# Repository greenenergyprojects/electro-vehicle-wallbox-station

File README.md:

# electro-vehicle-wallbox-station
Electro Vehicle Wallbox, Mode 3 / Typ 2 (230V/AC/20A)

## Overview

* Installing Raspberry PI  
  See: [docs/README-install-pi.md](docs/README-install-pi.md)

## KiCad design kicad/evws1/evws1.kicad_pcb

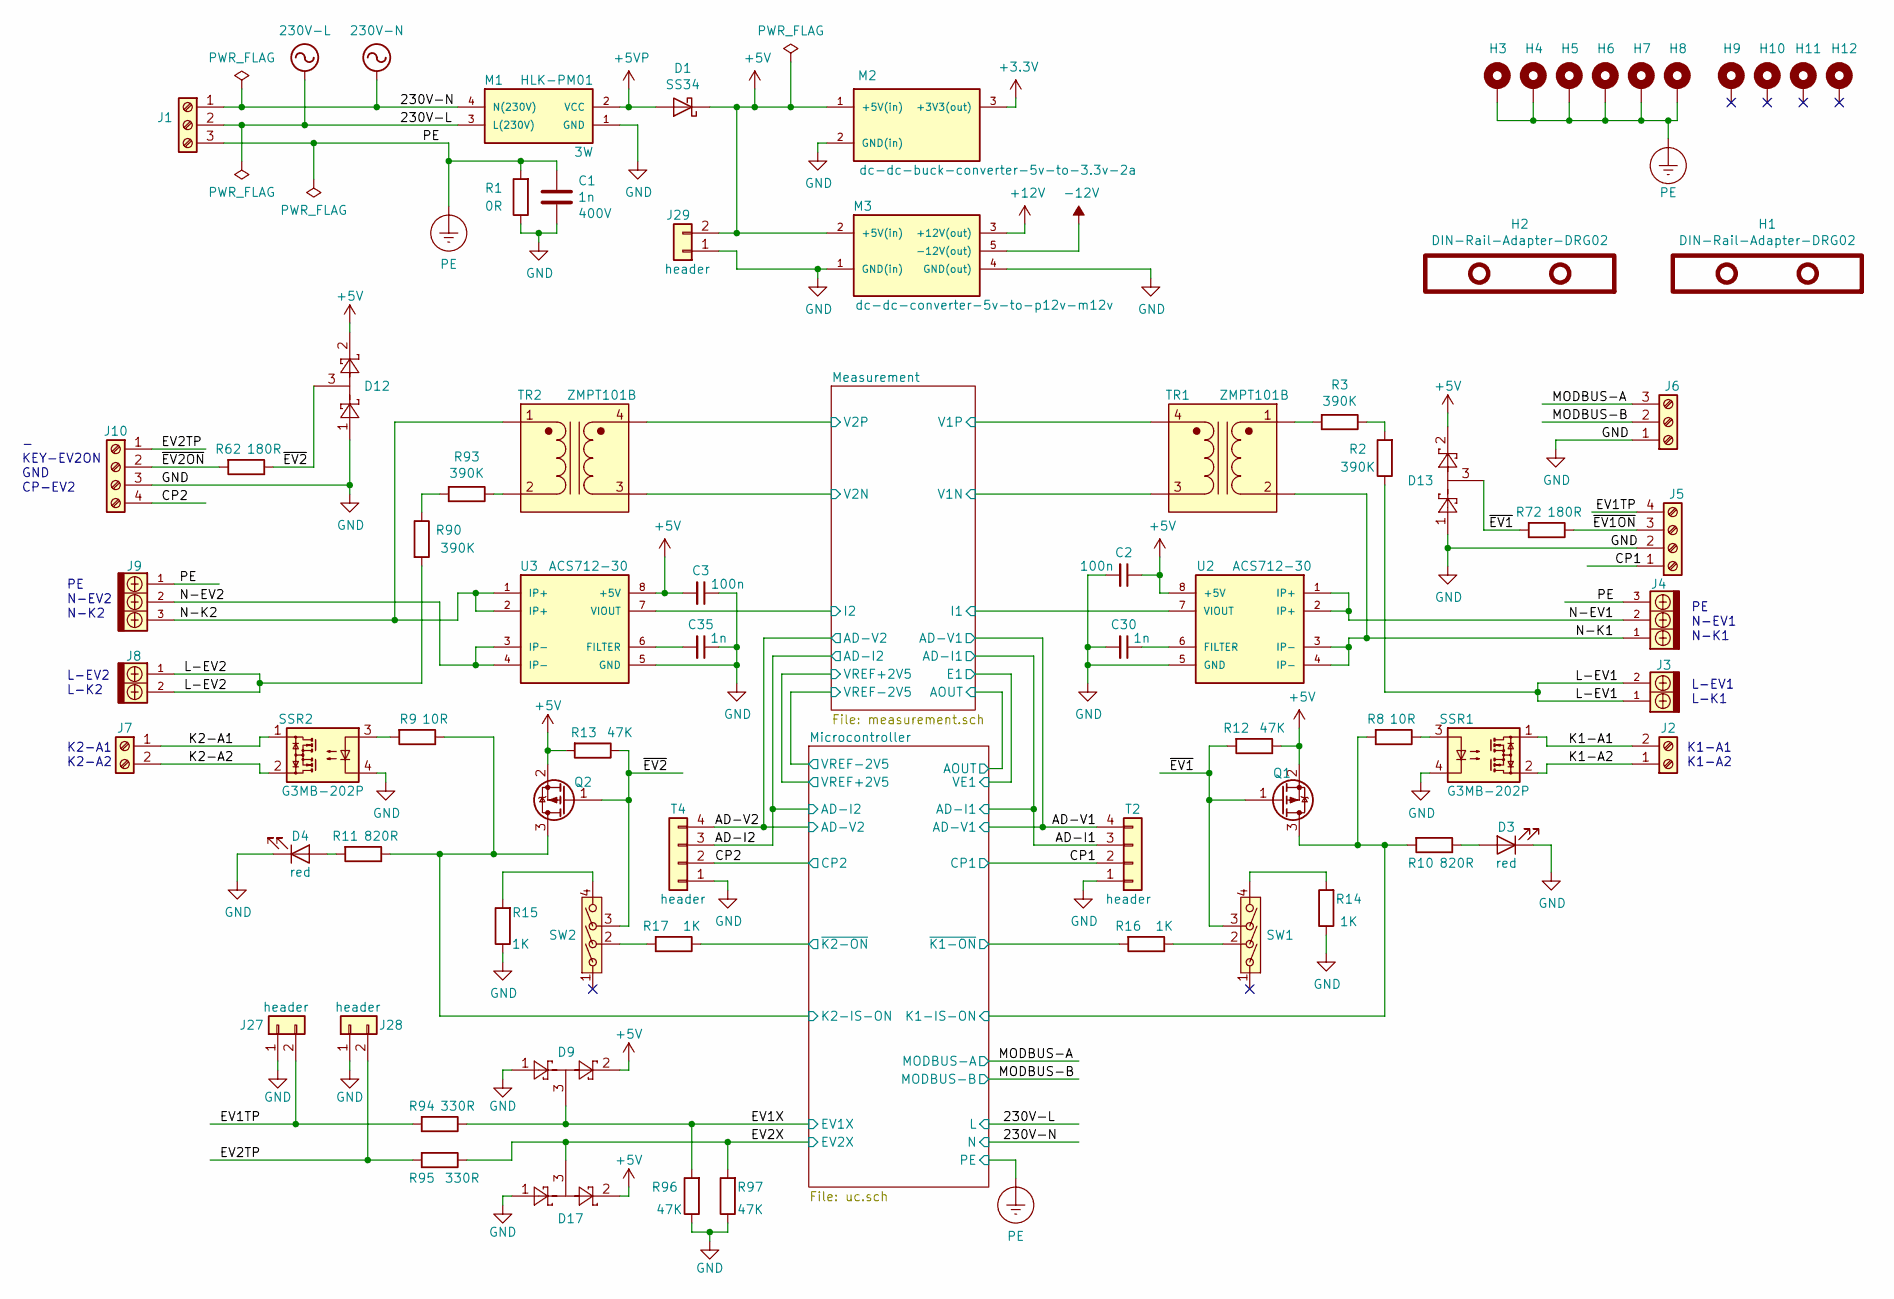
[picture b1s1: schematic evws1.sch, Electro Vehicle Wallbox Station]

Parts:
C1: 1n; c-1206-hand-soldering; Voltage 400V
C2, C3: 100n; c-1206-hand-soldering
C30, C35: 1n; c-1206-hand-soldering
D1: SS34; sma_hand-soldering
D3, D4: LED; LED_0805_HandSoldering
D9, D12, D13, D17: BAT54S; sot-23_hand-soldering
H1, H2: DIN-Rail-Adapter-DRG02; DIN-RAIL-ADAPTER-DRG-02-ebay-254055322883
H3, H4, H5, H6, H7, H8, H9, H10, H11, H12: MountingHole_Pad; MountingHole_2.5mm_Pad_Via
J1, J6: Screw_Terminal_01x03; Terminalblock-5mm-3P
J2, J7: Screw_Terminal_01x02; Terminalblock-5mm-2P
J3, J8: HB9500-2P
J4, J9: HB9500-3P
J5, J10: Screw_Terminal_01x04; Terminalblock-5mm-4P
J27, J28, J29: header; idc-header-1x02-p2.54mm-vertical
M1: HLK-PM01; HLK-PM01-5M05
M2: dc-dc-buck-converter-5v-to-3.3v-2a
M3: dc-dc-converter-5v-to-p12v-m12v
Q1, Q2: AO3401; TSOT-23_HandSoldering
R1: 0R; r-1206-hand-soldering
R2, R3, R90, R93: 390K; r-1206-hand-soldering
R8, R9: 10R; r-1206-hand-soldering
R10, R11: 820R; r-1206-hand-soldering
R12, R13, R96, R97: 47K; r-1206-hand-soldering
R14, R15, R16, R17: 1K; r-1206-hand-soldering
R62, R72: 180R; r-1206-hand-soldering
R94, R95: 330R; r-1206-hand-soldering
SSR1, SSR2: G3MB-202P; SSR_Omron_G3MB-202P
SW1, SW2: SW_SS13F06-G5; Switch-3pos-SS13F06-G5
T2, T4: header; idc-header-1x04-p2.54mm-vertical
TR1, TR2: ZMPT101B; Transformer-zmpt101b_ebay-121438904988
U2, U3: ACS712-30; ACS712

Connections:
230V-L: J1.2, M1.3 (L(230V)); also elsewhere on the board
230V-N: J1.1, M1.4 (N(230V)); also elsewhere on the board
+5V: C2.1, C3.2, D1.1 (K), D9.2, D12.2, D13.2, D17.2, J29.2, M2.1 (+5V(in)), M3.2 (+5V(in)), Q1.2 (S), Q2.2 (S), R12.1, R13.2, U2.8 (+5V), U3.8 (+5V); also elsewhere on the board
+5VP: D1.2 (A), M1.2 (VCC)
+12V: M3.3 (+12V(out)); also elsewhere on the board
-12V: M3.5 (-12V(out)); also elsewhere on the board
/AD-I1: T2.3; also elsewhere on the board
/AD-I2: T4.3; also elsewhere on the board
/AD-V1: T2.4; also elsewhere on the board
/AD-V2: T4.4; also elsewhere on the board
/CP1: J5.1, T2.2; also elsewhere on the board
/CP2: J10.4, T4.2; also elsewhere on the board
/EV1TP: J5.4, J27.2, R94.2
/EV1X: D9.3, R94.1, R96.2; also elsewhere on the board
/EV2TP: J10.1, J28.2, R95.2
/EV2X: D17.3, R95.1, R97.2; also elsewhere on the board
/K1-A1: J2.2, SSR1.1 (AC)
/K1-A2: J2.1, SSR1.2 (AC)
/K2-A1: J7.1, SSR2.1 (AC)
/K2-A2: J7.2, SSR2.2 (AC)
/L-EV1: J3.1, J3.2, R2.1
/L-EV2: J8.1, J8.2, R90.2
/MODBUS-A: J6.3; also elsewhere on the board
/MODBUS-B: J6.2; also elsewhere on the board
/Measurement/I1: U2.7 (VIOUT); also elsewhere on the board
/Measurement/I2: U3.7 (VIOUT); also elsewhere on the board
/Measurement/V1P: TR1.4 (SB); also elsewhere on the board
/Measurement/V2P: TR2.4 (SB); also elsewhere on the board
/Microcontroller/K1-IS-ON: Q1.3 (D), R8.2, R10.2; also elsewhere on the board
/Microcontroller/K2-IS-ON: Q2.3 (D), R9.1, R11.1; also elsewhere on the board
/Microcontroller/~K1-ON: R16.2; also elsewhere on the board
/Microcontroller/~K2-ON: R17.1; also elsewhere on the board
/N-EV1: J4.2, U2.1 (IP+), U2.2 (IP+)
/N-EV2: J9.2, U3.3 (IP-), U3.4 (IP-)
/N-K1: J4.1, TR1.2 (AB), U2.3 (IP-), U2.4 (IP-)
/N-K2: J9.3, TR2.1 (AA), U3.1 (IP+), U3.2 (IP+)
/~EV1: D13.3, Q1.1 (G), R12.2, R72.2, SW1.3
/~EV1ON: J5.3, R72.1
/~EV2: D12.3, Q2.1 (G), R13.1, R62.1, SW2.3
/~EV2ON: J10.2, R62.2
GND: C1.2, C2.2, C3.1, C30.2, C35.1, D3.1 (K), D4.1 (K), D9.1, D12.1, D13.1, D17.1, J5.2, J6.1, J10.3, J27.1, J28.1, J29.1, M1.1 (GND), M2.2 (GND(in)), M3.1 (GND(in)), M3.4 (GND(out)), R1.1, R14.1, R15.1, R96.1, R97.1, SSR1.4 (-), SSR2.4 (-), T2.1, T4.1, TR1.3 (SA), TR2.3 (SA), U2.5 (GND), U3.5 (GND); also elsewhere on the board
unnamed: C30.1, U2.6 (FILTER)
unnamed: C35.2, U3.6 (FILTER)
unnamed: D3.2 (A), R10.1
unnamed: D4.2 (A), R11.2
unnamed: R2.2, R3.1
unnamed: R3.2, TR1.1 (AA)
unnamed: R8.1, SSR1.3 (+)
unnamed: R9.2, SSR2.3 (+)
unnamed: R14.2, SW1.4
unnamed: R15.2, SW2.4
unnamed: R16.1, SW1.2
unnamed: R17.2, SW2.2
unnamed: R90.1, R93.2
unnamed: R93.1, TR2.2 (AB)
PE: C1.1, H3.1, H4.1, H5.1, H6.1, H7.1, H8.1, J1.3, J4.3, J9.1, R1.2; also elsewhere on the board

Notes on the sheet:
L-EV2 L-K2
PE N-EV2 N-K2
K2-A1 K2-A2
- KEY-EV2ON GND CP-EV2
L-EV1 L-K1
PE N-EV1 N-K1
K1-A1 K1-A2

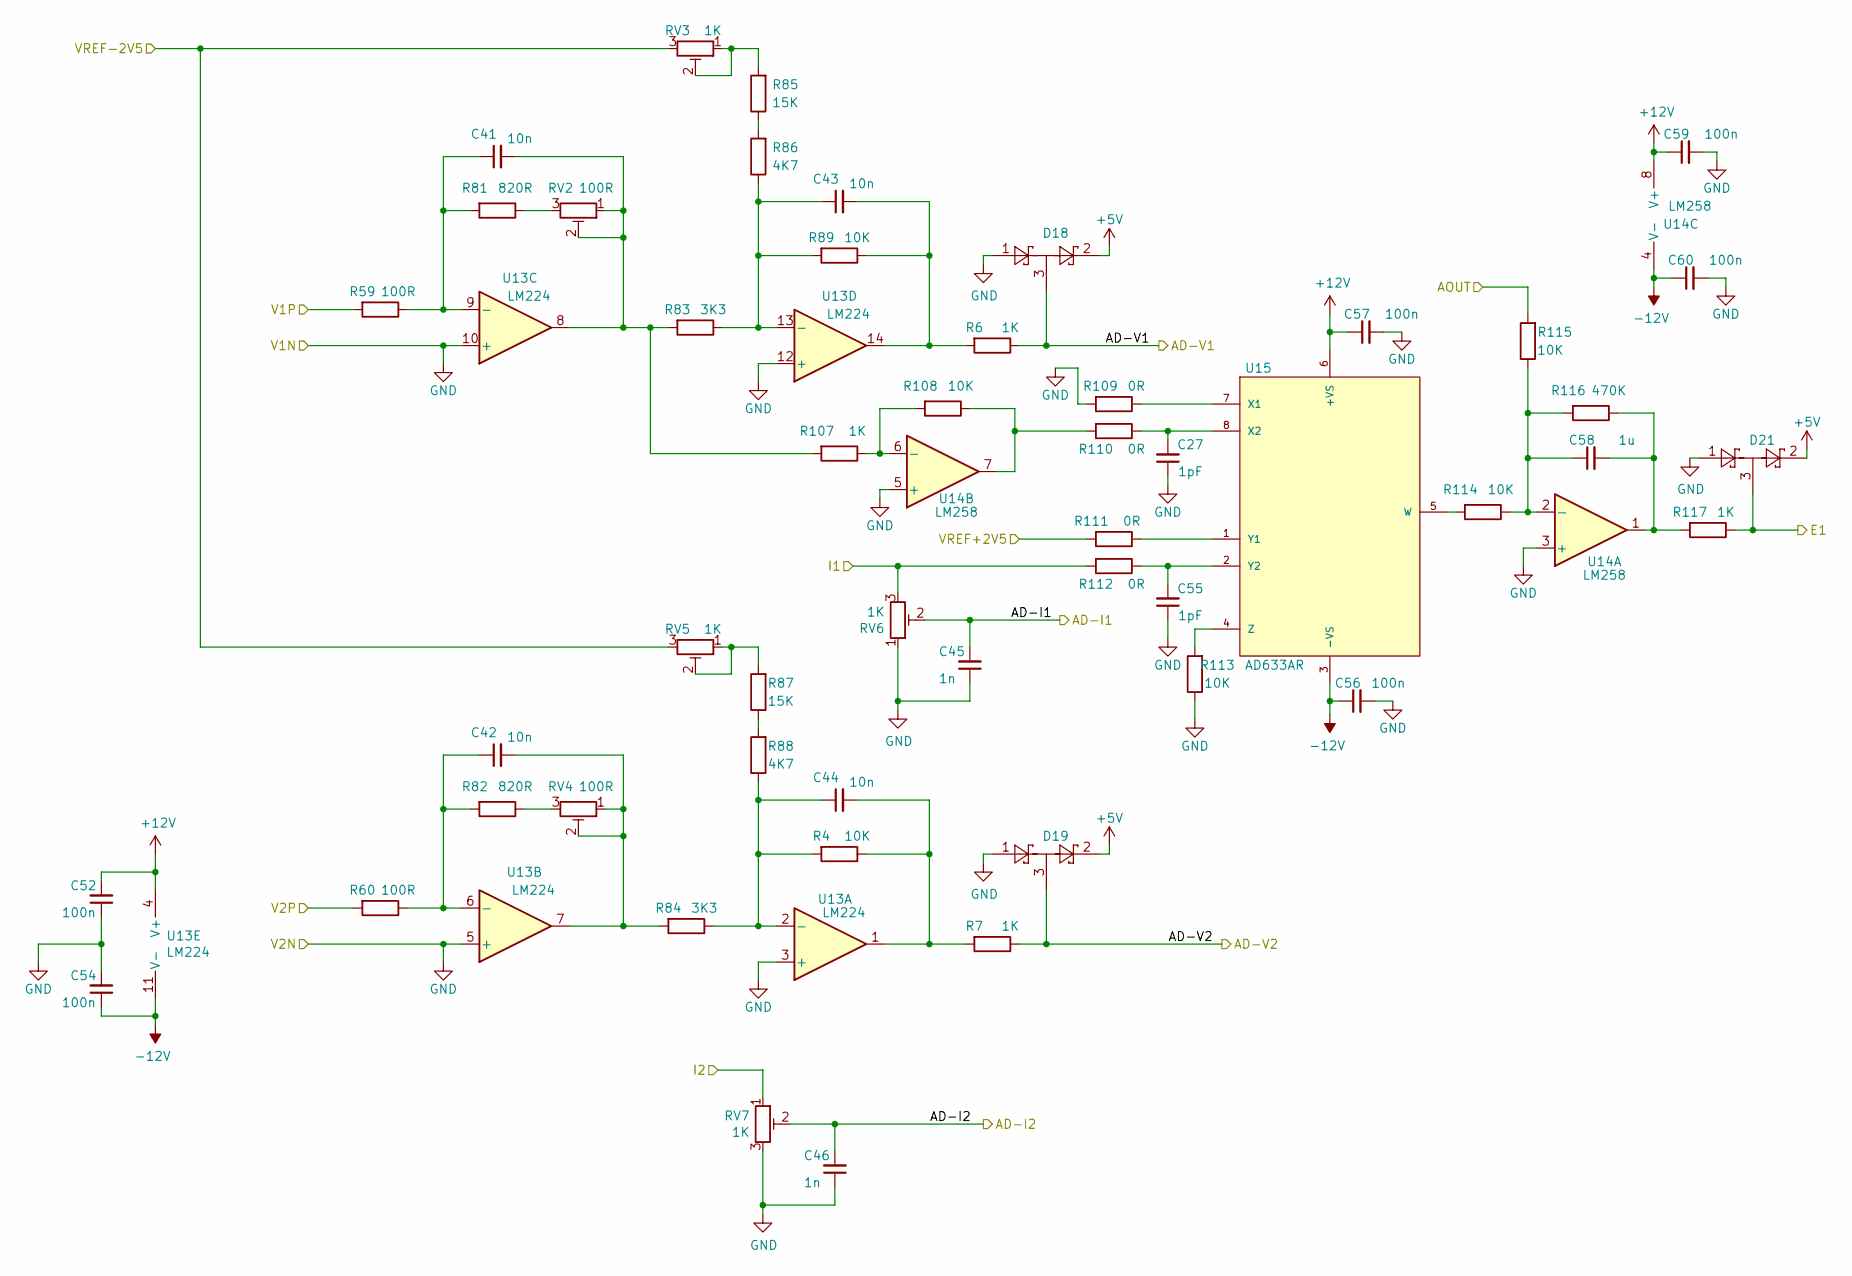
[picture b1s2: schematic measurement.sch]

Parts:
C27, C55: 1pF; c-1206-hand-soldering
C41, C42, C43, C44: 10n; c-1206-hand-soldering
C45, C46: 1n; c-1206-hand-soldering
C52, C54, C56, C57, C59, C60: 100n; c-1206-hand-soldering
C58: 1u; c-1206-hand-soldering
D18, D19, D21: BAT54S; sot-23_hand-soldering
R4, R89, R108, R113, R114, R115: 10K; r-1206-hand-soldering
R6, R7, R107, R117: 1K; r-1206-hand-soldering
R59, R60: 100R; r-1206-hand-soldering
R81, R82: 820R; r-1206-hand-soldering
R83, R84: 3K3; r-1206-hand-soldering
R85, R87: 15K; r-1206-hand-soldering
R86, R88: 4K7; r-1206-hand-soldering
R109, R110, R111, R112: 0R; r-1206-hand-soldering
R116: 470K; r-1206-hand-soldering
RV2, RV4: 100R; trimmer-tht-3296
RV3, RV5, RV6, RV7: 1K; trimmer-tht-3296
U13: LM224; soic-14_hand-soldering
U14: LM258; soic-8_hand-soldering
U15: AD633AR; soic-8_hand-soldering

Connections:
+5V: D18.2, D19.2, D21.2; also elsewhere on the board
+12V: C52.2, C57.1, C59.1, U13.4 (V+), U14.8 (V+), U15.6 (+VS); also elsewhere on the board
-12V: C54.1, C56.1, C60.1, U13.11 (V-), U14.4 (V-), U15.3 (-VS); also elsewhere on the board
/AD-I1: C45.2, RV6.2; also elsewhere on the board
/AD-I2: C46.2, RV7.2; also elsewhere on the board
/AD-V1: D18.3, R6.1; also elsewhere on the board
/AD-V2: D19.3, R7.1; also elsewhere on the board
/Measurement/AOUT: R115.2; also elsewhere on the board
/Measurement/E1: D21.3, R117.1; also elsewhere on the board
/Measurement/I1: R112.2, RV6.3; also elsewhere on the board
/Measurement/I2: RV7.1; also elsewhere on the board
/Measurement/V1P: R59.2; also elsewhere on the board
/Measurement/V2P: R60.2; also elsewhere on the board
/Measurement/VREF+2V5: R111.2; also elsewhere on the board
/Measurement/VREF-2V5: RV3.3, RV5.3; also elsewhere on the board
GND: C27.1, C45.1, C46.1, C52.1, C54.2, C55.1, C56.2, C57.2, C59.2, C60.2, D18.1, D19.1, D21.1, R109.2, R113.1, RV6.1, RV7.3, U13.3 (+), U13.5 (+), U13.10 (+), U13.12 (+), U14.3 (+), U14.5 (+); also elsewhere on the board
unnamed: C27.2, R110.1, U15.8 (X2)
unnamed: C41.1, R59.1, R81.2, U13.9 (-)
unnamed: C41.2, R83.2, R107.2, RV2.1, RV2.2, U13.8
unnamed: C42.1, R60.1, R82.2, U13.6 (-)
unnamed: C42.2, R84.2, RV4.1, RV4.2, U13.7
unnamed: C43.1, R83.1, R86.1, R89.2, U13.13 (-)
unnamed: C43.2, R6.2, R89.1, U13.14
unnamed: C44.1, R4.2, R84.1, R88.1, U13.2 (-)
unnamed: C44.2, R4.1, R7.2, U13.1
unnamed: C55.2, R112.1, U15.2 (Y2)
unnamed: C58.1, R114.1, R115.1, R116.2, U14.2 (-)
unnamed: C58.2, R116.1, R117.2, U14.1
unnamed: R81.1, RV2.3
unnamed: R82.1, RV4.3
unnamed: R85.1, R86.2
unnamed: R85.2, RV3.1, RV3.2
unnamed: R87.1, R88.2
unnamed: R87.2, RV5.1, RV5.2
unnamed: R107.1, R108.2, U14.6 (-)
unnamed: R108.1, R110.2, U14.7
unnamed: R109.1, U15.7 (X1)
unnamed: R111.1, U15.1 (Y1)
unnamed: R113.2, U15.4 (Z)
unnamed: R114.2, U15.5 (W)

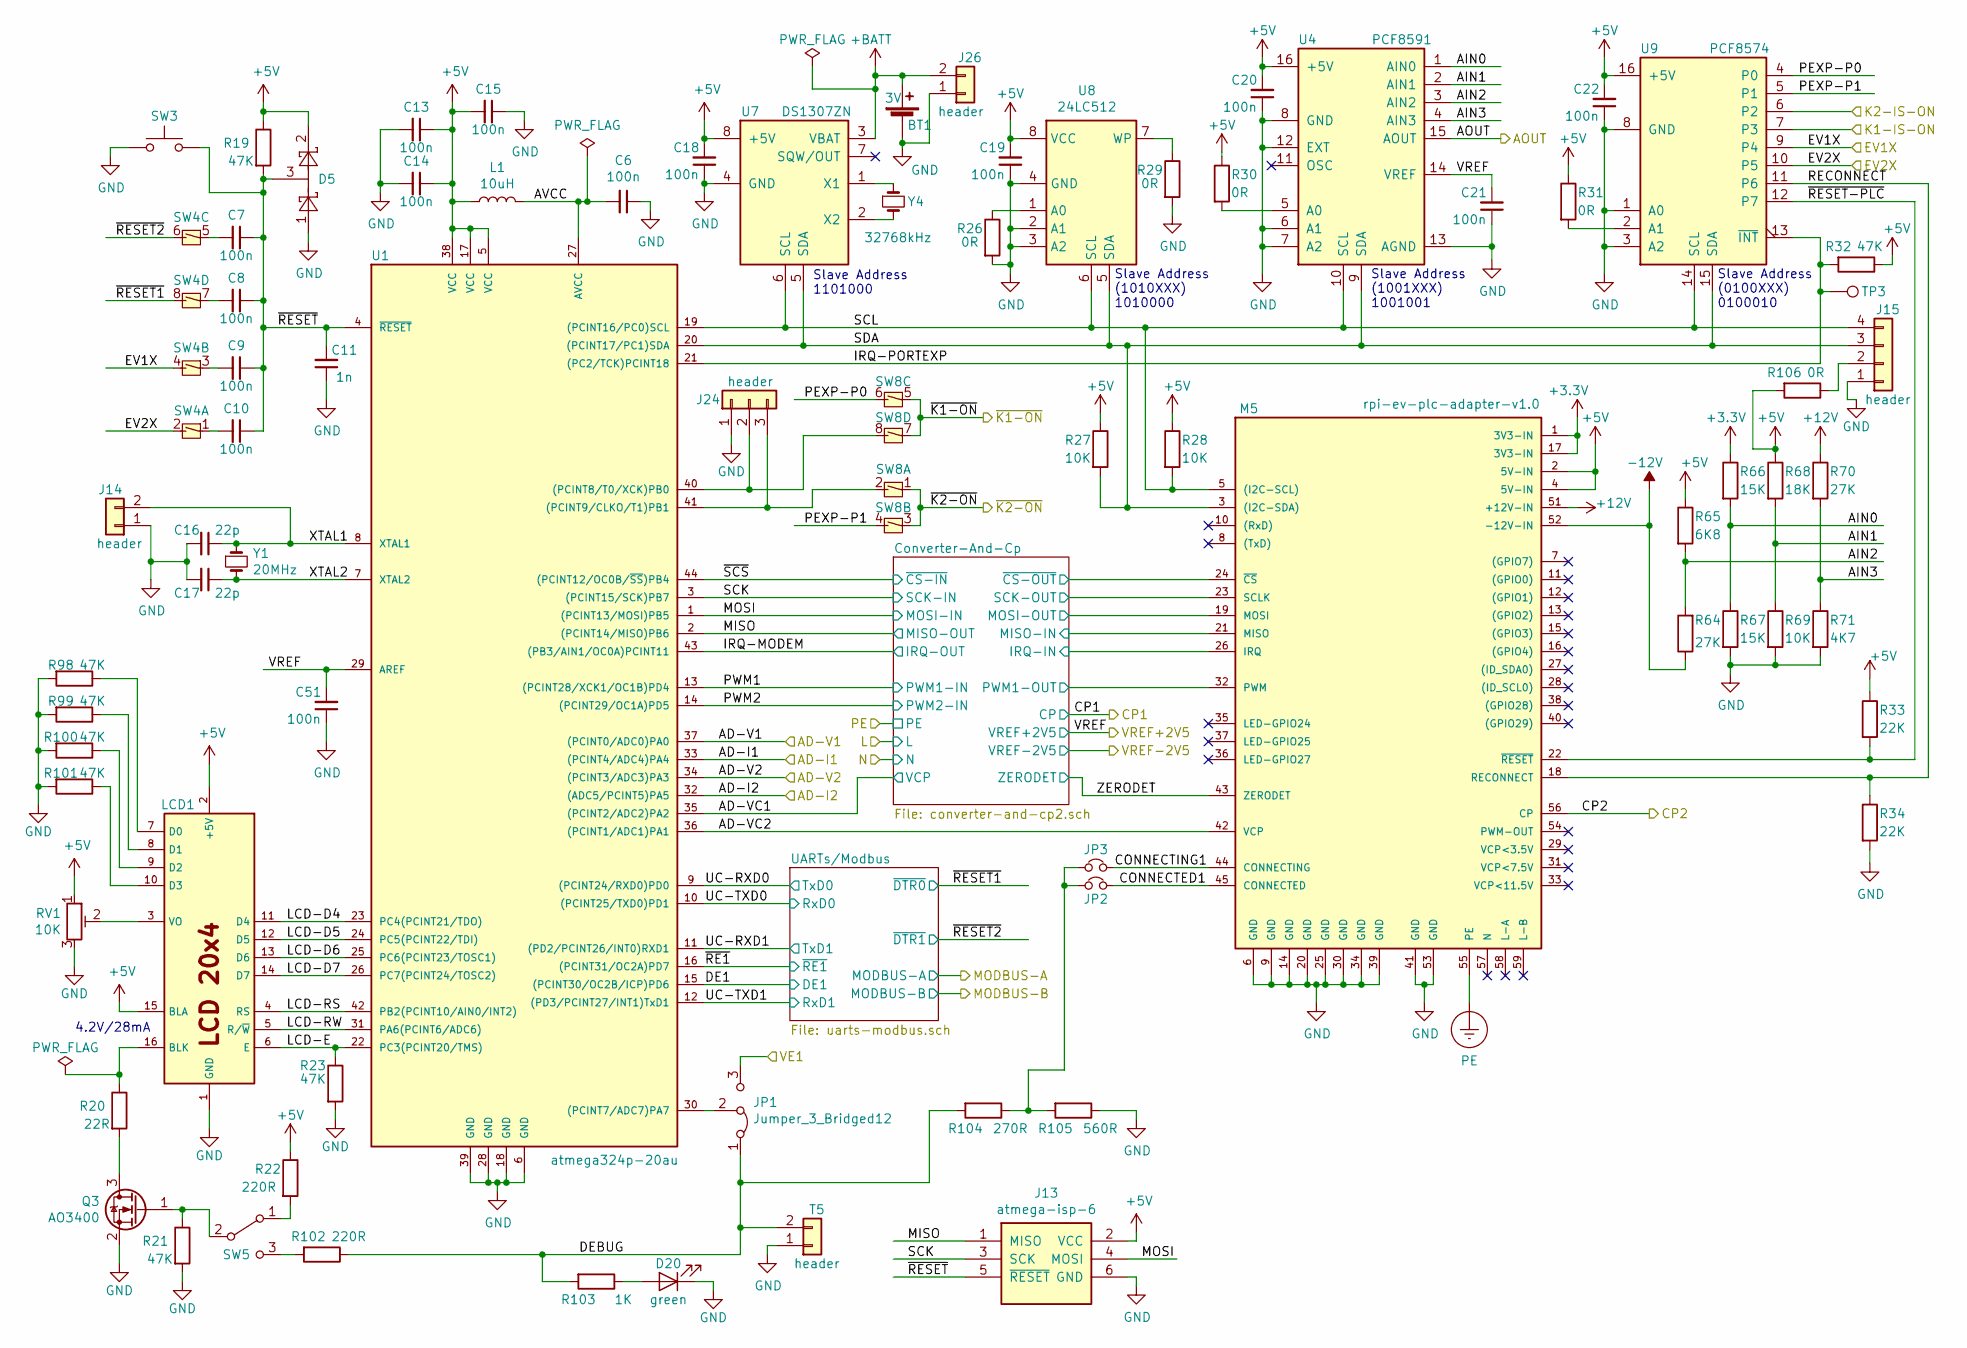
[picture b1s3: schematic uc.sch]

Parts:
BT1: 3V; knob-battery-holder-vertical-tht
C6, C7, C8, C9, C10, C13, C14, C15, C18, C19, C20, C21, C22, C51: 100n; c-1206-hand-soldering
C11: 1n; c-1206-hand-soldering
C16, C17: 22p; c-1206-hand-soldering
D5: BAT54S; sot-23_hand-soldering
D20: LED; LED_0805_HandSoldering
J13: atmega-isp-6; AVR-ISP-6
J14, J26: header; idc-header-1x02-p2.54mm-vertical
J15: header; idc-header-1x04-p2.54mm-vertical
J24: header; idc-header-1x03-p2.54mm-vertical
JP1: Jumper_3_Bridged12; idc-header-1x03-p2.54mm-vertical
JP2, JP3: header; idc-header-1x02-p2.54mm-vertical
L1: 10uH; L_1206_HandSoldering
LCD1: lcd-4x20-5v-backlight-4bit
M5: rpi-ev-plc-adapter-v1.0
Q3: AO3400; sot-23_hand-soldering
R19, R21, R23, R32, R98, R99, R100, R101: 47K; r-1206-hand-soldering
R20: 22R; r-1206-hand-soldering
R22, R102: 220R; r-1206-hand-soldering
R26, R29, R30, R31, R106: 0R; r-1206-hand-soldering
R27, R28, R69: 10K; r-1206-hand-soldering
R33, R34: 22K; r-1206-hand-soldering
R64, R70: 27K; r-1206-hand-soldering
R65: 6K8; r-1206-hand-soldering
R66, R67: 15K; r-1206-hand-soldering
R68: 18K; r-1206-hand-soldering
R71: 4K7; r-1206-hand-soldering
R103: 1K; r-1206-hand-soldering
R104: 270R; r-1206-hand-soldering
R105: 560R; r-1206-hand-soldering
RV1: 10K; trimmer-tht-3296
SW3: SW_Push; push-button-smd-4.5x4.5mm-black
SW4, SW8: dip-switch-4x2pos-smd-1.27mm
SW5: SS-12D00G3; switch_ss-12d00g3
T5: header; idc-header-1x02-p2.54mm-vertical
TP3: TestPoint; Measurement_Point_Round-TH_Small
U1: atmega324p-20au; TQFP-44_10x10mm_Pitch0.8mm
U4: PCF8591; soic-16w_hand-soldering
U7: DS1307ZN; soic-8_hand-soldering
U8: 24LC512; soic-8_hand-soldering
U9: PCF8574; soic-16w_hand-soldering
Y1: 20MHz; hc49s-smd
Y4: 32768kHz; crystal-32.768khz-2x6mm-tht-vertical

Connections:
+5V: C13.1, C14.1, C15.2, C18.2, C19.2, C20.2, C22.2, D5.2, J13.2 (VCC), L1.1, LCD1.2 (+5V), LCD1.15 (BLA), M5.2 (5V-IN), M5.4 (5V-IN), R19.1, R22.1, R27.1, R28.1, R30.1, R31.1, R32.1, R33.1, R65.1, R68.1, R106.2, RV1.1, U1.5 (VCC), U1.17 (VCC), U1.38 (VCC), U4.16 (+5V), U7.8 (+5V), U8.8 (VCC), U9.16 (+5V); also elsewhere on the board
+12V: M5.51 (+12V-IN), R70.1; also elsewhere on the board
+BATT: BT1.1 (+), J26.2, U7.3 (VBAT)
-12V: M5.52 (-12V-IN), R64.1; also elsewhere on the board
/AD-I1: U1.33 ((PCINT4/ADC4)PA4); also elsewhere on the board
/AD-I2: U1.32 ((ADC5/PCINT5)PA5); also elsewhere on the board
/AD-V1: U1.37 ((PCINT0/ADC0)PA0); also elsewhere on the board
/AD-V2: U1.34 ((PCINT3/ADC3)PA3); also elsewhere on the board
/CP2: M5.56 (CP); also elsewhere on the board
/EV1X: SW4.4, U9.9 (P4); also elsewhere on the board
/EV2X: SW4.2, U9.10 (P5); also elsewhere on the board
/Measurement/AOUT: U4.15 (AOUT); also elsewhere on the board
/Measurement/E1: JP1.3 (B); also elsewhere on the board
/Measurement/VREF+2V5: C21.2, C51.2, U1.29 (AREF), U4.14 (VREF); also elsewhere on the board
/Microcontroller/AD-VC1: U1.35 ((PCINT2/ADC2)PA2); also elsewhere on the board
/Microcontroller/AD-VC2: M5.42 (VCP), U1.36 ((PCINT1/ADC1)PA1)
/Microcontroller/AIN0: R66.2, R67.1, U4.1 (AIN0)
/Microcontroller/AIN1: R68.2, R69.1, U4.2 (AIN1)
/Microcontroller/AIN2: R64.2, R65.2, U4.3 (AIN2)
/Microcontroller/AIN3: R70.2, R71.1, U4.4 (AIN3)
/Microcontroller/AVCC: C6.2, L1.2, U1.27 (AVCC)
/Microcontroller/CONNECTED1: JP2.2, M5.45 (CONNECTED)
/Microcontroller/CONNECTING1: JP3.2, M5.44 (CONNECTING)
/Microcontroller/Converter-And-Cp/IRQ-IN: M5.26 (IRQ); also elsewhere on the board
/Microcontroller/Converter-And-Cp/MISO-IN: M5.21 (MISO); also elsewhere on the board
/Microcontroller/Converter-And-Cp/MOSI-OUT: M5.19 (MOSI); also elsewhere on the board
/Microcontroller/Converter-And-Cp/PWM1-OUT: M5.32 (PWM); also elsewhere on the board
/Microcontroller/Converter-And-Cp/SCK-OUT: M5.23 (SCLK); also elsewhere on the board
/Microcontroller/Converter-And-Cp/~CS-OUT: M5.24 (~CS); also elsewhere on the board
/Microcontroller/DE1: U1.15 ((PCINT30/OC2B/ICP)PD6); also elsewhere on the board
/Microcontroller/DEBUG: JP1.1 (A), R102.1, R103.2, R104.2, T5.2
/Microcontroller/IRQ-MODEM: U1.43 ((PB3/AIN1/OC0A)PCINT11); also elsewhere on the board
/Microcontroller/IRQ-PORTEXP: R32.2, TP3.1, U1.21 ((PC2/TCK)PCINT18), U9.13 (~INT~)
/Microcontroller/K1-IS-ON: U9.7 (P3); also elsewhere on the board
/Microcontroller/K2-IS-ON: U9.6 (P2); also elsewhere on the board
/Microcontroller/LCD-D4: LCD1.11 (D4), U1.23 (PC4(PCINT21/TDO))
/Microcontroller/LCD-D5: LCD1.12 (D5), U1.24 (PC5(PCINT22/TDI))
/Microcontroller/LCD-D6: LCD1.13 (D6), U1.25 (PC6(PCINT23/TOSC1))
/Microcontroller/LCD-D7: LCD1.14 (D7), U1.26 (PC7(PCINT24/TOSC2))
/Microcontroller/LCD-E: LCD1.6 (E), R23.1, U1.22 (PC3(PCINT20/TMS))
/Microcontroller/LCD-RS: LCD1.4 (RS), U1.42 (PB2(PCINT10/AIN0/INT2))
/Microcontroller/LCD-RW: LCD1.5 (R/~W~), U1.31 (PA6(PCINT6/ADC6))
/Microcontroller/MISO: J13.1 (MISO), U1.2 ((PCINT14/MISO)PB6); also elsewhere on the board
/Microcontroller/MOSI: J13.4 (MOSI), U1.1 ((PCINT13/MOSI)PB5); also elsewhere on the board
/Microcontroller/PEXP-P0: SW8.6 (4), U9.4 (P0)
/Microcontroller/PEXP-P1: SW8.4, U9.5 (P1)
/Microcontroller/PWM1: U1.13 ((PCINT28/XCK1/OC1B)PD4); also elsewhere on the board
/Microcontroller/PWM2: U1.14 ((PCINT29/OC1A)PD5); also elsewhere on the board
/Microcontroller/RECONNECT: M5.18 (RECONNECT), R34.1, U9.11 (P6)
/Microcontroller/SCK: J13.3 (SCK), U1.3 ((PCINT15/SCK)PB7); also elsewhere on the board
/Microcontroller/SCL: J15.4, M5.5 ((I2C-SCL)), R28.2, U1.19 ((PCINT16/PC0)SCL), U4.10 (SCL), U7.6 (SCL), U8.6 (SCL), U9.14 (SCL)
/Microcontroller/SDA: J15.3, M5.3 ((I2C-SDA)), R27.2, U1.20 ((PCINT17/PC1)SDA), U4.9 (SDA), U7.5 (SDA), U8.5 (SDA), U9.15 (SDA)
/Microcontroller/UC-RXD0: U1.9 ((PCINT24/RXD0)PD0); also elsewhere on the board
/Microcontroller/UC-RXD1: U1.11 ((PD2/PCINT26/INT0)RXD1); also elsewhere on the board
/Microcontroller/UC-TXD0: U1.10 ((PCINT25/TXD0)PD1); also elsewhere on the board
/Microcontroller/UC-TXD1: U1.12 ((PD3/PCINT27/INT1)TxD1); also elsewhere on the board
/Microcontroller/XTAL1: C16.1, J14.2, U1.8 (XTAL1), Y1.1
/Microcontroller/XTAL2: C17.1, U1.7 (XTAL2), Y1.2
/Microcontroller/ZERODET: M5.43 (ZERODET); also elsewhere on the board
/Microcontroller/~K1-ON: SW8.5 (3), SW8.7 (3); also elsewhere on the board
/Microcontroller/~K2-ON: SW8.1, SW8.3; also elsewhere on the board
/Microcontroller/~RE1: U1.16 ((PCINT31/OC2A)PD7); also elsewhere on the board
/Microcontroller/~RESET: C7.1, C8.1, C9.1, C10.1, C11.2, D5.3, J13.5 (~RESET~), R19.2, SW3.2, U1.4 (~RESET)
/Microcontroller/~RESET1: SW4.8 (4); also elsewhere on the board
/Microcontroller/~RESET2: SW4.6 (4); also elsewhere on the board
/Microcontroller/~RESET-PLC: M5.22 (~RESET), R33.2, U9.12 (P7)
/Microcontroller/~SCS: U1.44 ((PCINT12/OC0B/~SS~)PB4); also elsewhere on the board
GND: BT1.2 (-), C6.1, C11.1, C13.2, C14.2, C15.1, C16.2, C17.2, C18.1, C19.1, C20.1, C21.1, C22.1, C51.1, D5.1, D20.1 (K), J13.6 (GND), J14.1, J15.1, J24.1, J26.1, LCD1.1 (GND), M5.6 (GND), M5.9 (GND), M5.14 (GND), M5.20 (GND), M5.25 (GND), M5.30 (GND), M5.34 (GND), M5.39 (GND), M5.41 (GND), M5.53 (GND), Q3.2 (S), R21.2, R23.2, R26.2, R29.2, R34.2, R67.2, R69.2, R71.2, R98.2, R99.2, R100.2, R101.2, R105.1, RV1.3, SW3.1, T5.1, U1.6 (GND), U1.18 (GND), U1.28 (GND), U1.39 (GND), U4.6 (A1), U4.7 (A2), U4.8 (GND), U4.12 (EXT), U4.13 (AGND), U7.4 (GND), U8.2 (A1), U8.3 (A2), U8.4 (GND), U9.1 (A0), U9.3 (A2), U9.8 (GND); also elsewhere on the board
unnamed: C7.2, SW4.5 (3)
unnamed: C8.2, SW4.7 (3)
unnamed: C9.2, SW4.3
unnamed: C10.2, SW4.1
unnamed: D20.2 (A), R103.1
unnamed: J15.2, R106.1
unnamed 147: J24.2, SW8.8 (4), U1.40 ((PCINT8/T0/XCK)PB0); also elsewhere on the board
unnamed 148: J24.3, SW8.2, U1.41 ((PCINT9/CLKO/T1)PB1); also elsewhere on the board
unnamed: JP1.2 (C), U1.30 ((PCINT7/ADC7)PA7)
unnamed: JP2.1, JP3.1, R104.1, R105.2
unnamed: LCD1.3 (VO), RV1.2
unnamed: LCD1.7 (D0), R98.1
unnamed: LCD1.8 (D1), R99.1
unnamed: LCD1.9 (D2), R100.1
unnamed: LCD1.10 (D3), R101.1
unnamed: LCD1.16 (BLK), R20.1
unnamed: Q3.1 (G), R21.1, SW5.2 (B)
unnamed: Q3.3 (D), R20.2
unnamed: R22.2, SW5.1 (A)
unnamed: R26.1, U8.1 (A0)
unnamed: R29.1, U8.7 (WP)
unnamed: R30.2, U4.5 (A0)
unnamed: R31.2, U9.2 (A1)
unnamed: R102.2, SW5.3 (C)
unnamed: U7.1 (X1), Y4.1
unnamed: U7.2 (X2), Y4.2
PE: M5.55 (PE); also elsewhere on the board

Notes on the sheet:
4.2V/28mA
Slave Address 1101000
Slave Address (1001XXX) 1001001
Slave Address (1010XXX) 1010000
Slave Address (0100XXX) 0100010

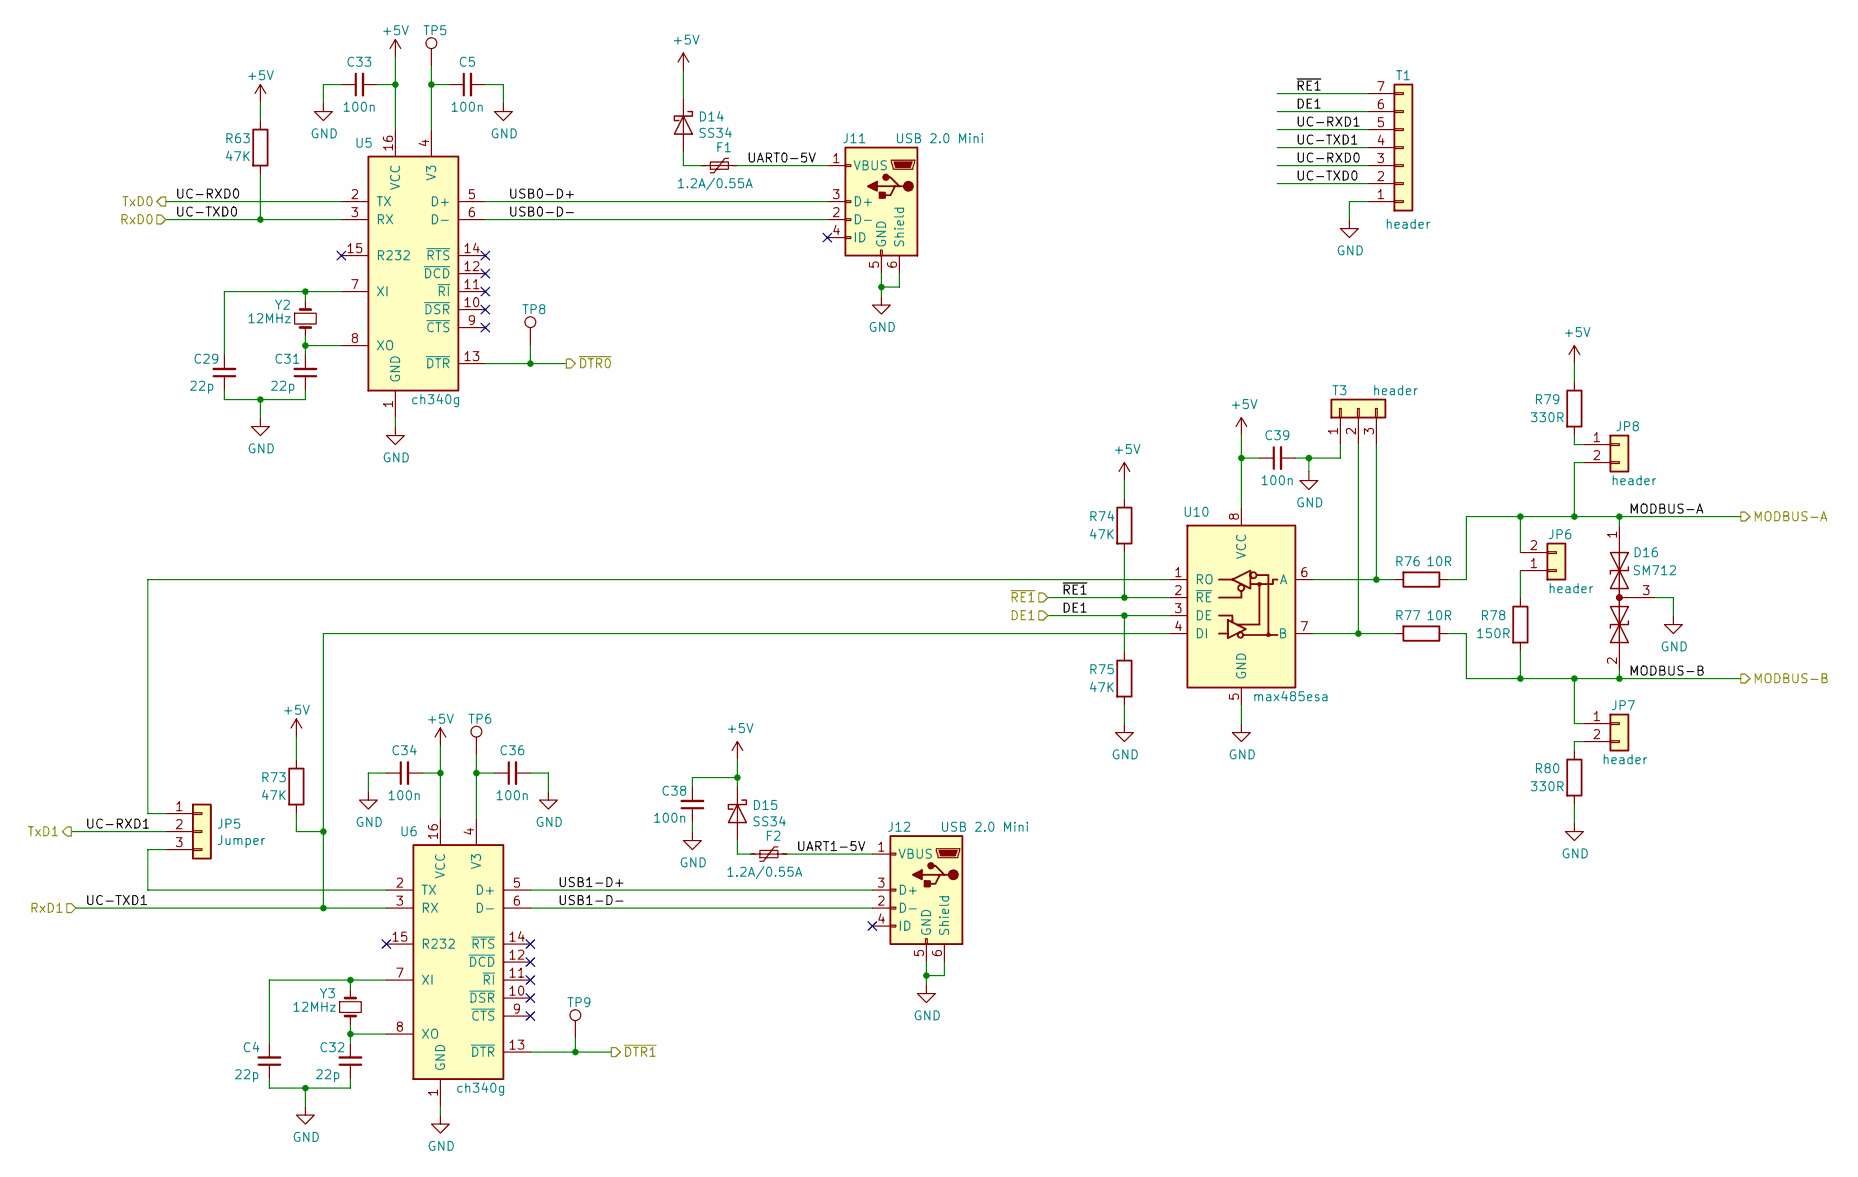
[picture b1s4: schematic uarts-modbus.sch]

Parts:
C4, C29, C31, C32: 22p; c-1206-hand-soldering
C5, C33, C34, C36, C38, C39: 100n; c-1206-hand-soldering
D14, D15: SS34; sma_hand-soldering
D16: SM712; sot-23_hand-soldering
F1, F2: MF-SMDF050-2; mf-smdf
J11, J12: USB 2.0 Mini; usb-mini-tht
JP5: Jumper; idc-header-1x03-p2.54mm-vertical
JP6, JP7, JP8: header; idc-header-1x02-p2.54mm-vertical
R63, R73, R74, R75: 47K; r-1206-hand-soldering
R76, R77: 10R; r-1206-hand-soldering
R78: 150R; r-1206-hand-soldering
R79, R80: 330R; r-1206-hand-soldering
T1: header; idc-header-1x07-p2.54mm-vertical
T3: header; idc-header-1x03-p2.54mm-vertical
TP5, TP6, TP8, TP9: TestPoint; SolderWirePad_single_0-8mmDrill
U5, U6: ch340g; soic-16_hand-soldering
U10: max485esa; soic-8_hand-soldering
Y2, Y3: 12MHz; Oscillator-SMD-M49S

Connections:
+5V: C33.2, C34.2, C38.2, C39.1, D14.1 (K), D15.1 (K), R63.1, R73.1, R74.1, R79.1, U5.16 (VCC), U6.16 (VCC), U10.8 (VCC); also elsewhere on the board
/MODBUS-A: D16.1 (A1), JP6.2, JP8.2, R76.1; also elsewhere on the board
/MODBUS-B: D16.2 (A2), JP7.1, R77.1, R78.2; also elsewhere on the board
/Microcontroller/DE1: R75.1, T1.6, U10.3 (DE); also elsewhere on the board
/Microcontroller/UARTs/Modbus/UART0-5V: F1.2, J11.1 (VBUS)
/Microcontroller/UARTs/Modbus/UART1-5V: F2.2, J12.1 (VBUS)
/Microcontroller/UARTs/Modbus/USB0-D+: J11.3 (D+), U5.5 (D+)
/Microcontroller/UARTs/Modbus/USB0-D-: J11.2 (D-), U5.6 (D-)
/Microcontroller/UARTs/Modbus/USB1-D+: J12.3 (D+), U6.5 (D+)
/Microcontroller/UARTs/Modbus/USB1-D-: J12.2 (D-), U6.6 (D-)
/Microcontroller/UC-RXD0: T1.3, U5.2 (TX); also elsewhere on the board
/Microcontroller/UC-RXD1: JP5.2, T1.5; also elsewhere on the board
/Microcontroller/UC-TXD0: R63.2, T1.2, U5.3 (RX); also elsewhere on the board
/Microcontroller/UC-TXD1: R73.2, T1.4, U6.3 (RX), U10.4 (DI); also elsewhere on the board
/Microcontroller/~RE1: R74.2, T1.7, U10.2 (~RE); also elsewhere on the board
/Microcontroller/~RESET1: TP8.1, U5.13 (~DTR~); also elsewhere on the board
/Microcontroller/~RESET2: TP9.1, U6.13 (~DTR~); also elsewhere on the board
GND: C4.1, C5.2, C29.1, C31.1, C32.1, C33.1, C34.1, C36.2, C38.1, C39.2, D16.3 (common), J11.5 (GND), J11.6 (Shield), J12.5 (GND), J12.6 (Shield), R75.2, R80.2, T1.1, T3.1, U5.1 (GND), U6.1 (GND), U10.5 (GND); also elsewhere on the board
unnamed: C4.2, U6.7 (XI), Y3.1
unnamed: C5.1, TP5.1, U5.4 (V3)
unnamed: C29.2, U5.7 (XI), Y2.1
unnamed: C31.2, U5.8 (XO), Y2.2
unnamed: C32.2, U6.8 (XO), Y3.2
unnamed: C36.1, TP6.1, U6.4 (V3)
unnamed: D14.2 (A), F1.1
unnamed: D15.2 (A), F2.1
unnamed: JP5.1, U10.1 (RO)
unnamed: JP5.3, U6.2 (TX)
unnamed: JP6.1, R78.1
unnamed: JP7.2, R80.1
unnamed: JP8.1, R79.2
unnamed: R76.2, T3.3, U10.6 (A)
unnamed: R77.2, T3.2, U10.7 (B)
